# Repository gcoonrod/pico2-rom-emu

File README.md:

# Pico2-ROM-Emu

Pico2-ROM-Emu is a project designed to emulate 28 pin EEPROM (28C256 compatible) functionality using the Raspberry Pi Pico2 and a fast SRAM.

## Theory of Operation
The theory of operation is relatively simple:

1. Assert active-low reset signal
2. Fill SRAM with ROM data using octal latches 
3. Hi-Z the latches and de-assert reset
4. SRAM is directly connected to DUT EEPROM socket via ribbon cable 

## Circuit Schematic

## MicroPython Firmware (`pico-rom-emu-firmware`)
This sub-project contains the firmware written in MicroPython. It is responsible for:
- Copying provided ROM binary images to the embedded SRAM
- Accepting new ROM images over USB serial connection
- Controlling DUT reset signal

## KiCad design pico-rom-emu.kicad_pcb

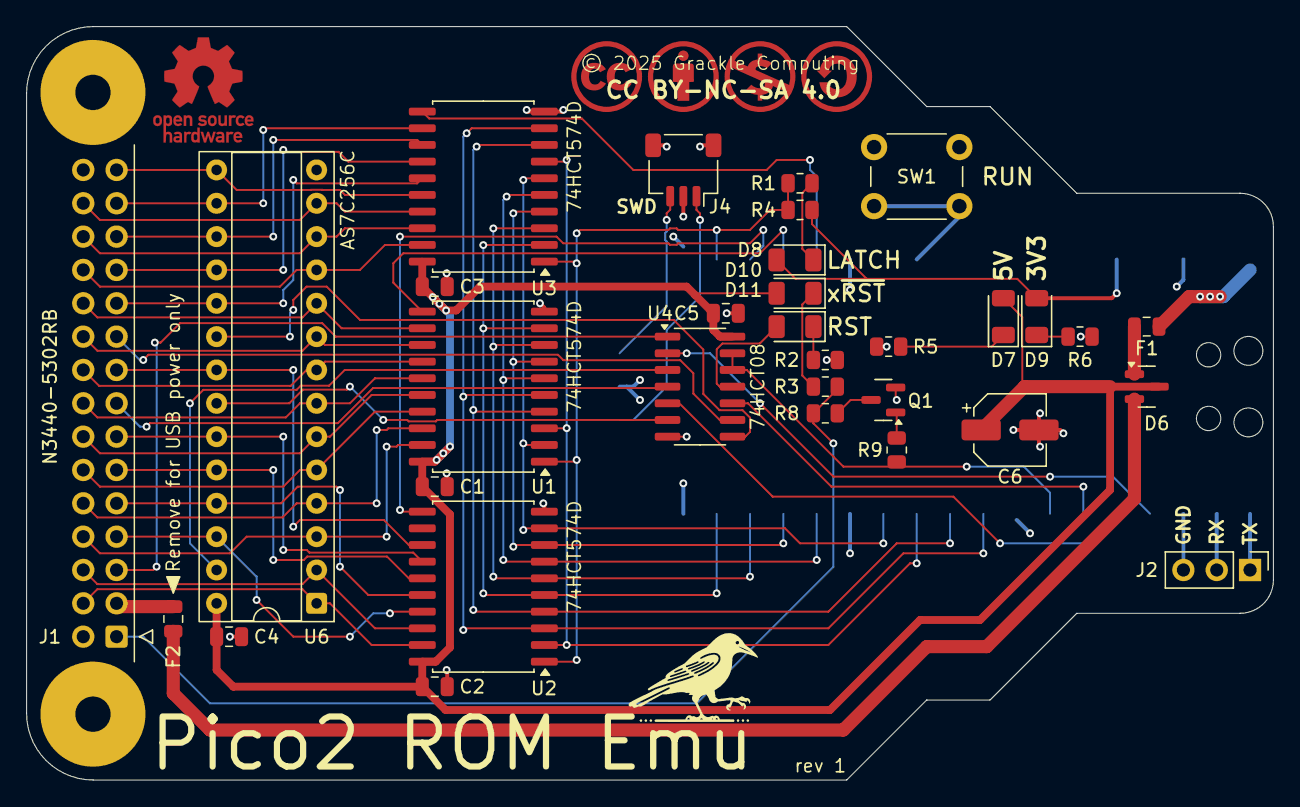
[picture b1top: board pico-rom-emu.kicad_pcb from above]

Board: 4 copper layers, 95.0 x 57.4 mm, 34 parts (1 on the bottom side), 66 nets.

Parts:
C1, C2, C3, C4, C5: 0u1; C_0805_2012Metric
C6: 10u; CP_Elec_5x5.4
D6: PMEG2005CT,215; SOT-23
D7, D9: LED_RED; LED_1206_3216Metric
D8, D10, D11: LED_AMB; LED_1206_3216Metric
F1, F2: MF-PSMF020X-2; Fuse_0805_2012Metric
G1: LOGO; GrackleLogo12mm
J1: N3440-5302RB; IDC-Header_2x15-1MP_P2.54mm_Latch_Horizontal
J2: HDR_UART; PinHeader_1x03_P2.54mm_Vertical
J4: HDR_SWD; JST_SH_SM03B-SRSS-TB_1x03-1MP_P1.00mm_Horizontal
Q1: MMBT2222A; SOT-23
R1, R5, R9: 1k8; R_0805_2012Metric
R2, R3, R6: 680R; R_0805_2012Metric
R4: 3k3; R_0805_2012Metric
R8: 10R; R_0805_2012Metric
SW1: SW_Push; SW_PUSH_6mm
U1, U2, U3: 74HCT574D; SOIC-20W_7.5x12.8mm_P1.27mm
U4: 74HCT08; SOIC-14_3.9x8.7mm_P1.27mm
U5: RaspberryPi_Pico2; RaspberryPi_Pico_SMD_HandSolder
U6: AS7C256C; DIP-28_W7.62mm_Socket

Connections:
+3V3: D8.2 (A), D9.2 (A), R4.1, U5.36 (3V3)
+5V: C1.2, C2.2, C3.2, C4.2, C5.2, C6.1, D6.3 (K), D7.2 (A), D10.2 (A), U1.20 (VCC), U2.20 (VCC), U3.20 (VCC), U4.14 (VCC), U6.28 (VCC)
/LADD: U3.11 (Cp), U5.27 (GPIO21)
/LADH: U2.11 (Cp), U5.25 (GPIO19)
/LADL: U1.11 (Cp), U5.26 (GPIO20)
/L~OE: R1.2, R4.2, U1.1 (OE), U2.1 (OE), U3.1 (OE), U5.24 (GPIO18)
/RAM_~CS: U4.10, U5.6 (GPIO4)
/RAM_~OE: U4.5, U5.5 (GPIO3)
/RAM_~WE: U4.2, U5.4 (GPIO2)
/RST: R9.1, U4.12, U4.13, U5.7 (GPIO5)
/RSTbuf: D11.2 (A), U4.11
/RSTr: Q1.1 (B), R9.2
/RUN: SW1.1, U5.30 (RUN)
/SWCLK: J4.1, U5.D1 (SWCLK)
/SWDIO: J4.3, U5.D3 (SWDIO)
/UART0_RX: J2.2, U5.2 (GPIO1)
/UART0_TX: J2.1, U5.1 (GPIO0)
/X~CS: J1.19, U4.9
/X~OE: J1.15, U4.4
/X~RST: J1.1, R3.2, R8.2
/X~RSTr: Q1.3 (C), R8.1
/X~WE: J1.5, U4.1
/f_vbus: D6.1 (A), F1.2
/f_x5v: D6.2 (A), F2.1
/led_3v3: D9.1 (K), R6.1
/led_5v: D7.1 (K), R5.1
/led_loe: D8.1 (K), R1.1
/led_rst: D11.1 (K), R2.1
/led_xrst: D10.1 (K), R3.1
/~CS: U4.8, U6.20 (~CS)
/~OE: U4.6, U6.22 (~OE)
/~WE: U4.3, U6.27 (~WE)
GND: C1.1, C2.1, C3.1, C4.1, C5.1, C6.2, J1.2, J1.30, J2.3, J4.2, J4.MP (MountPin), Q1.2 (E), R2.2, R5.2, R6.2, SW1.2, U1.10 (GND), U2.10 (GND), U3.10 (GND), U4.7 (GND), U5.3 (GND), U5.8 (GND), U5.13 (GND), U5.18 (GND), U5.23 (GND), U5.28 (GND), U5.38 (GND), U5.D2 (GND), U6.14 (GND)
VBUS: F1.1, U5.40 (VBUS)
X5V: F2.2, J1.3
XA0: J1.22, U1.12 (Q7), U6.10 (A0)
XA1: J1.20, U1.13 (Q6), U6.9 (A1)
XA2: J1.18, U1.14 (Q5), U6.8 (A2)
XA3: J1.16, U1.15 (Q4), U6.7 (A3)
XA4: J1.14, U1.16 (Q3), U6.6 (A4)
XA5: J1.12, U1.17 (Q2), U6.5 (A5)
XA6: J1.10, U1.18 (Q1), U6.4 (A6)
XA7: J1.8, U1.19 (Q0), U6.3 (A7)
XA8: J1.9, U2.16 (Q3), U6.25 (A8)
XA9: J1.11, U2.15 (Q4), U6.24 (A9)
XA10: J1.17, U2.13 (Q6), U6.21 (A10)
XA11: J1.13, U2.14 (Q5), U6.23 (A11)
XA12: J1.6, U2.18 (Q1), U6.2 (A12)
XA13: J1.7, U2.17 (Q2), U6.26 (A13)
XA14: J1.4, U2.19 (Q0), U6.1 (A14)
XD0: J1.24, U3.19 (Q0), U6.11 (D0)
XD1: J1.26, U3.18 (Q1), U6.12 (D1)
XD2: J1.28, U3.17 (Q2), U6.13 (D2)
XD3: J1.29, U3.16 (Q3), U6.15 (D3)
XD4: J1.27, U3.12 (Q7), U6.16 (D4)
XD5: J1.25, U3.13 (Q6), U6.17 (D5)
XD6: J1.23, U3.14 (Q5), U6.18 (D6)
XD7: J1.21, U3.15 (Q4), U6.19 (D7)
XDA0: U1.9 (D7), U2.5 (D3), U3.2 (D0), U5.17 (GPIO13)
XDA1: U1.8 (D6), U2.6 (D4), U3.3 (D1), U5.16 (GPIO12)
XDA2: U1.7 (D5), U2.8 (D6), U3.4 (D2), U5.15 (GPIO11)
XDA3: U1.6 (D4), U2.7 (D5), U3.5 (D3), U5.14 (GPIO10)
XDA4: U1.5 (D3), U2.3 (D1), U3.9 (D7), U5.9 (GPIO6)
XDA5: U1.4 (D2), U2.4 (D2), U3.8 (D6), U5.10 (GPIO7)
XDA6: U1.3 (D1), U2.2 (D0), U3.7 (D5), U5.11 (GPIO8)
XDA7: U1.2 (D0), U2.9 (D7), U3.6 (D4), U5.12 (GPIO9)

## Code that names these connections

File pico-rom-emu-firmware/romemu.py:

# pico-rom-emu-firmware (c) by Greg Coonrod
#
# pico-rom-emu-firmware is licensed under a
# Creative Commons Attribution-NonCommercial-ShareAlike 4.0 International License.
#
# You should have received a copy of the license along with this
# work. If not, see <https://creativecommons.org/licenses/by-nc-sa/4.0/>.

from machine import Pin, UART
from utime import sleep_us, ticks_ms, sleep_ms
from sys import print_exception, stdin, stdout
import select
import struct  # For packing/unpacking address

DEBUG = False

# RAM control pins for WEb, OEb, and CSb
pin_ram_web = Pin(7, Pin.OUT)
pin_ram_oeb = Pin(8, Pin.OUT)
pin_ram_csb = Pin(9, Pin.OUT)

# Latch control pins for LADL, LADH, and LADD
pin_ladl = Pin(10, Pin.OUT)
pin_ladh = Pin(11, Pin.OUT)
pin_ladd = Pin(12, Pin.OUT)

# Reset pin
pin_rstb = Pin(14, Pin.OUT)

# eXternal Data and Address pins (XDA)
pin_xda7 = Pin(15, Pin.OUT)
pin_xda6 = Pin(16, Pin.OUT)
pin_xda5 = Pin(17, Pin.OUT)
pin_xda4 = Pin(18, Pin.OUT)
pin_xda3 = Pin(19, Pin.OUT)
pin_xda2 = Pin(20, Pin.OUT)
pin_xda1 = Pin(21, Pin.OUT)
pin_xda0 = Pin(22, Pin.OUT)

# Latch Output Enable pin
pin_loeb = Pin(26, Pin.OUT)


# --- Pin Initialization ---
def init_pins():
    pin_ram_web.on()
    pin_ram_oeb.on()
    pin_ram_csb.on()
    pin_ladl.off()
    pin_ladh.off()
    pin_ladd.off()
    pin_rstb.on()  # Start with reset de-asserted (system running)
    write_xda(0)  # Set XDA pins to output low
    pin_loeb.on()  # Latch outputs disabled initially


# --- XDA Bus Control ---
def write_xda(data):
    pin_xda7.value((data >> 7) & 0x01)
    pin_xda6.value((data >> 6) & 0x01)
    pin_xda5.value((data >> 5) & 0x01)
    pin_xda4.value((data >> 4) & 0x01)
    pin_xda3.value((data >> 3) & 0x01)
    pin_xda2.value((data >> 2) & 0x01)
    pin_xda1.value((data >> 1) & 0x01)
    pin_xda0.value(data & 0x01)


# --- RAM Write Function ---
def write_ram(addr, data):
    address_high = (addr >> 8) & 0xFF
    address_low = addr & 0xFF

    # Write high address byte
    write_xda(address_high)
    pin_ladh.on()
    sleep_us(1)
    pin_ladh.off()

    # Write low address byte
    write_xda(address_low)
    pin_ladl.on()
    sleep_us(1)
    pin_ladl.off()

    # Write data byte
    write_xda(data)
    pin_ladd.on()
    sleep_us(1)
    pin_ladd.off()

    # Pulse WEb to write
    pin_ram_web.off()
    sleep_us(1)
    pin_ram_web.on()


# --- Serial ROM Upload Function ---
def receive_rom_serial():
    """
    Waits for serial upload command 'U'.
    Receives a 2-byte little-endian starting address.
    Receives ROM data byte-by-byte until host sends 'E'.
    Writes received data to RAM.
    """
    # Use USB CDC serial
    # Set up polling object for stdin
    poll_obj = select.poll()
    poll_obj.register(stdin, select.POLLIN)

    print("Ready for serial ROM upload. Send 'U' to start.")

    # Wait for Upload command 'U'
    start_cmd = None
    while start_cmd != b"U":
        # Check if data is available on stdin
        poll_results = poll_obj.poll(1)  # Timeout after 1ms
        if poll_results:
            start_cmd = stdin.buffer.read(1)
        sleep_ms(10)  # Small delay to prevent busy-waiting

    print("Start command received.")
    stdout.buffer.write(b"A")  # Send Acknowledge

    # Receive 2-byte starting address (little-endian)
    addr_bytes = stdin.buffer.read(2)
    if len(addr_bytes) < 2:
        print("Error: Did not receive address.")
        return 0, 0  # Indicate error

    start_addr = struct.unpack("<H", addr_bytes)[
        0
    ]  # '<H' is little-endian unsigned short
    print(f"Receiving ROM data starting at address: 0x{start_addr:04X}")

    addr = start_addr
    bytes_written = 0
    start_time = ticks_ms()

    # Assert reset during upload
    pin_rstb.off()
    sleep_us(100)

    # Select RAM and enable latch output
    pin_ram_csb.off()
    pin_loeb.off()

    try:
        while True:
            # Wait for a byte, but check for End command 'E'
            # Use polling with a short timeout to remain responsive
            poll_results = poll_obj.poll(1000)  # Wait up to 1 second for data
            if not poll_results:
                print("Warning: Timeout waiting for data.")
                # Consider breaking or adding more robust error handling
                continue  # Keep waiting for now

            byte = stdin.buffer.read(1)

            if not byte:  # Should not happen with poll, but good practice
                print("Error: Serial connection closed unexpectedly.")
                break

            if byte == b"E":  # Check for End command
                print("End command received.")
                stdout.buffer.write(b"K")  # Send Confirmation
                break

            # Write the received byte to RAM
            write_ram(addr, byte[0])
            addr += 1
            bytes_written += 1

            # Optional: Add progress indicator
            if DEBUG and (bytes_written % 256 == 0):
                print(f"Received {bytes_written} bytes...")

    except Exception as e:
        print("Error during serial reception:")
        print_exception(e)
        bytes_written = 0  # Indicate failure
    finally:
        # De-select RAM, disable latch output (important first!)
        pin_ram_csb.on()
        pin_loeb.on()
        # De-assert reset *after* disabling RAM/latches
        pin_rstb.on()
        sleep_us(100)  # Give time for reset to propagate

    end_time = ticks_ms()
    return bytes_written, start_time, end_time, start_addr


# --- Main Execution ---
def main():
    init_pins()
    print("Pico ROM Emulator Ready.")
    print("Send 'U' over serial to upload a ROM.")

    while True:
        # Wait for and perform serial upload
        bytes_written, start_time, end_time, start_addr = receive_rom_serial()

        if bytes_written > 0:
            elapsed_ms = end_time - start_time
            elapsed_s = elapsed_ms / 1000.0
            write_speed = bytes_written / elapsed_s if elapsed_s > 0 else 0
            print(
                f"\nSuccessfully wrote {bytes_written} bytes starting at 0x{start_addr:04X} to RAM."
            )
            print(f"Time taken: {elapsed_s:.2f} seconds")
            print(f"Average write speed: {write_speed:.2f} bytes/second")
            print("\nSystem reset released. Emulator running...")
            print("Send 'U' again to upload another ROM.")
        else:
            print("\nROM upload failed or was cancelled.")
            print("Send 'U' to try again.")

        # The loop continues, waiting for the next 'U' command


if __name__ == "__main__":
    main()

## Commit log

2025-04-17 initial
2025-04-17 rev 1 kicad
2025-04-17 rev 0 firmware
2025-04-22 pre rev1 order
2025-05-05 initial serial upload work
2025-05-06 rev 1 pre-production clean up
2025-05-06 readme update
2025-05-06 remove old schematic
2025-05-07 minor changes for rev 1 spin at oshpark

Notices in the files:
pico-rom-emu.kicad_pcb:
CC BY-NC-SA 4.0
© 2025 Grackle Computing
